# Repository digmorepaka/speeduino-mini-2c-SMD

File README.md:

# Features
* 48x78mm form factor
* 2 Injection channels (High-Z negative side switching)
* 2 Ignition channels (5V/12V)
* Up to 2 cylinder sequential, up to 4 cylinder paired mode
* Tacho output
* 1 Programable output
* Secondary serial
* Speeduino firmware

# Use cases
* Motorcycles
* ATVs
* Go karts
* Other small form factor installations

Updated verison of: https://github.com/digmorepaka/speeduino-mini-2-channel

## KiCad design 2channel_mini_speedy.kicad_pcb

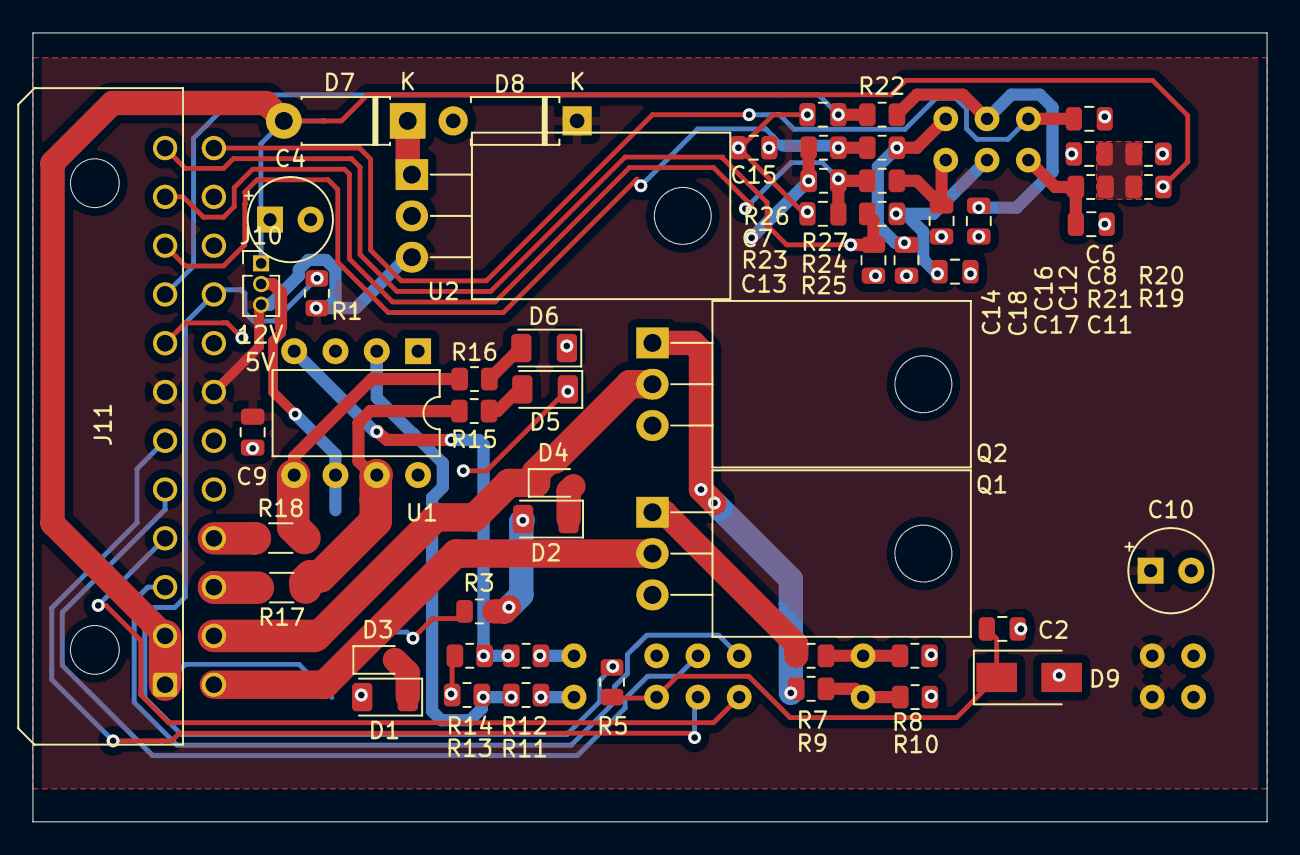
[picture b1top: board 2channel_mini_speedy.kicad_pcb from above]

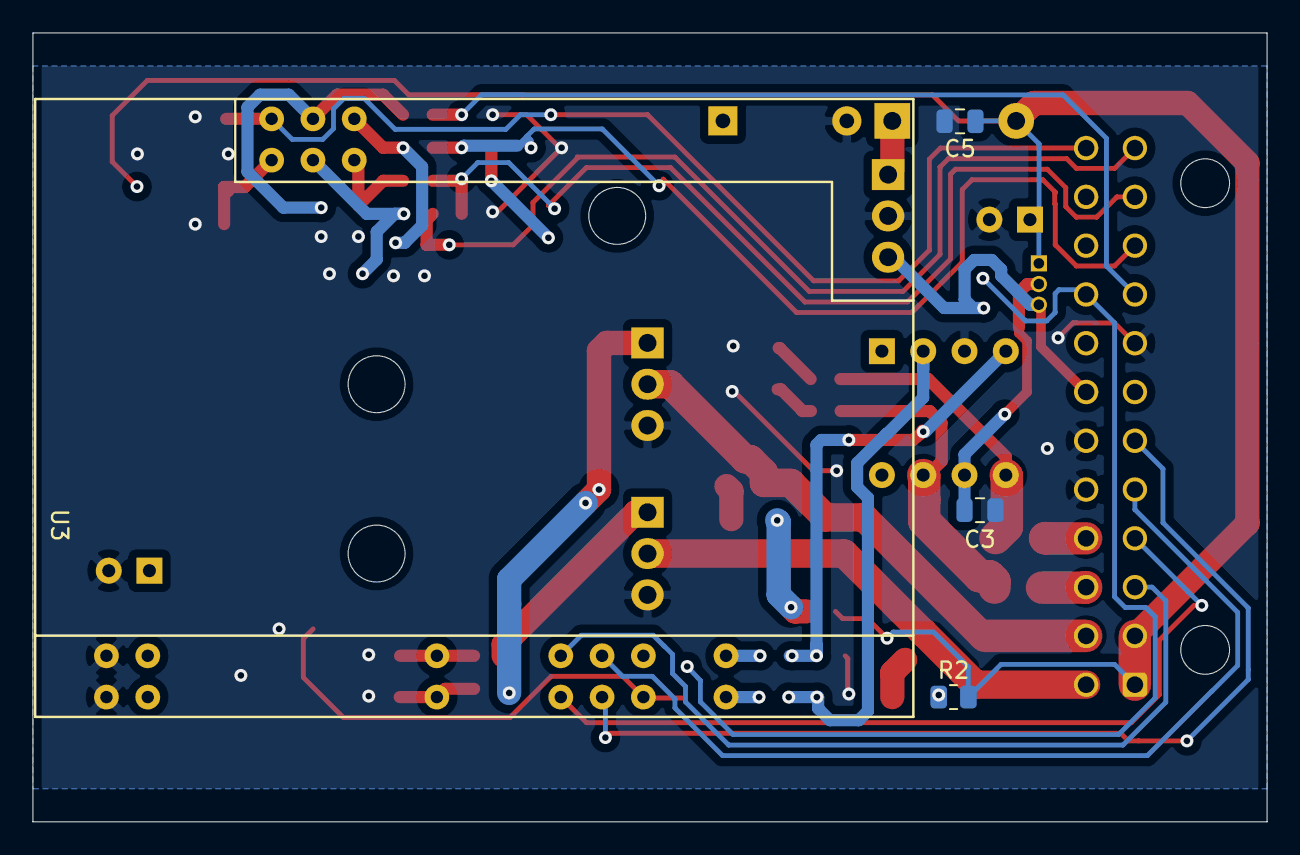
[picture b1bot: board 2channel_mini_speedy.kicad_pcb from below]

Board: 2 copper layers, 75.9 x 48.5 mm, 58 parts (4 on the bottom side), 42 nets.

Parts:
C2: 0.01uF; C_0805_2012Metric
C3: 1uF; C_0805_2012Metric
C4: 10uF 35V; CP_Radial_Tantal_D5.0mm_P2.50mm
C5, C9: 0.1uF 50V; C_0805_2012Metric
C6: 0.3uF; C_0805_2012Metric
C7, C8, C13, C14, C15: 0.1uF; C_0805_2012Metric
C10: 47uF 10V; CP_Radial_Tantal_D5.0mm_P2.50mm
C11, C12, C16, C17, C18: 0.22uF; C_0805_2012Metric
D1, D2, D5, D6: LED; LED_1206_3216Metric
D3, D4: 1N4004; D_SOD-323
D7: 1N5818; D_DO-41_SOD81_P7.62mm_Horizontal
D8: 1N5919BG; D_A-405_P7.62mm_Horizontal
D9: 5V1; D_SMA
J10: IGN Voltage sel; PinHeader_1x03_P1.27mm_Vertical
J11: Molex MicroFit 3.0 43045-2400/Amphenol ICC 101277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; Molex_Micro-Fit_3.0_43045-2400_2x12_P3.00mm_Horizontal
Q1, Q2: STP75N04-TO220; TO-220-3_Horizontal_TabDown
R1, R5, R7, R9, R11, R12, R20: 1K; R_0805_2012Metric
R2, R3: 680R; R_0805_2012Metric
R8, R10, R13, R14: 100K; R_0805_2012Metric
R15, R16: 2.4K; R_0805_2012Metric
R17, R18: 160R 2W; R_1206_3216Metric
R19: 3.9K; R_0805_2012Metric
R21, R22, R24, R25, R27: 470R; R_0805_2012Metric
R23, R26: 2.49K; R_0805_2012Metric
U1: TC4424EPA; DIP-8_W7.62mm
U2: LM2940T; TO-220-3_Horizontal_TabDown
U3: Mega2560-PRO; Mega2560-PRO-Stripped

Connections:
+5V: C9.1, C10.1, D8.1, J10.3, J11.7, J11.19, R1.2, R23.1, R26.1, U2.3, U3.5V
+12V: C4.1, C5.1, D7.2, J10.1, J11.1, J11.2, R2.2, R3.2, R19.1
BRV-SIG: C11.1, R21.1, U3.A1
CLT: C15.1, J11.10, R26.2, R27.2
CLT-SIG: C18.1, R27.1, U3.A4
D16: J11.5, U3.D16
GND: C2.1, C3.2, C4.2, C5.2, C6.2, C7.2, C8.2, C9.2, C10.2, C11.2, C12.2, C13.2, C14.2, C15.2, C16.2, C17.2, C18.2, D5.1, D6.1, D8.2, D9.2, J11.8, J11.17, J11.18, Q1.3, Q2.3, R8.1, R10.1, R13.2, R14.1, R20.2, U1.3, U2.2, U3.GND
IAT: C13.1, J11.11, R23.2, R24.2
IAT-SIG: C16.1, R24.1, U3.A5
IGN1: J11.15, R17.2
IGN1-SIG: R11.2, U3.D23
IGN2: J11.16, R18.1
IGN2-SIG: R12.2, U3.D22
IGN_PWR: C3.1, J10.2, U1.6
INJ1: D3.1, J11.13, Q1.2
INJ1-SIG: R7.2, R8.2, U3.D8
INJ2: D4.1, J11.14, Q2.2
INJ2-SIG: R9.2, R10.2, U3.D9
MAP-SIG: C6.1, J11.24, U3.A0
unnamed: C8.1, R19.2, R20.1, R21.2
unnamed: D1.1, D3.2
unnamed: D1.2, R2.1
unnamed: D2.1, D4.2
unnamed: D2.2, R3.1
unnamed: D5.2, R15.2
unnamed: D6.2, R16.2
unnamed: D7.1, U2.1
unnamed: Q1.1, R7.1
unnamed: Q2.1, R9.1
unnamed: R11.1, R13.1, U1.2
unnamed: R12.1, R14.2, U1.4
unnamed: R15.1, R17.1, U1.7
unnamed: R16.1, R18.2, U1.5
O2: C7.1, J11.9, R22.2
O2-SIG: C12.1, R22.1, U3.A2
RX3: J11.4, U3.D15
TACH1: C2.2, D9.1, R5.1, U3.D19
TACHO-OUT: J11.6, U3.D17
TPS: C14.1, J11.12, R25.2
TPS-SIG: C17.1, R25.1, U3.A3
TX3: J11.3, U3.D14
VR1+: J11.21, R1.1, R5.2
